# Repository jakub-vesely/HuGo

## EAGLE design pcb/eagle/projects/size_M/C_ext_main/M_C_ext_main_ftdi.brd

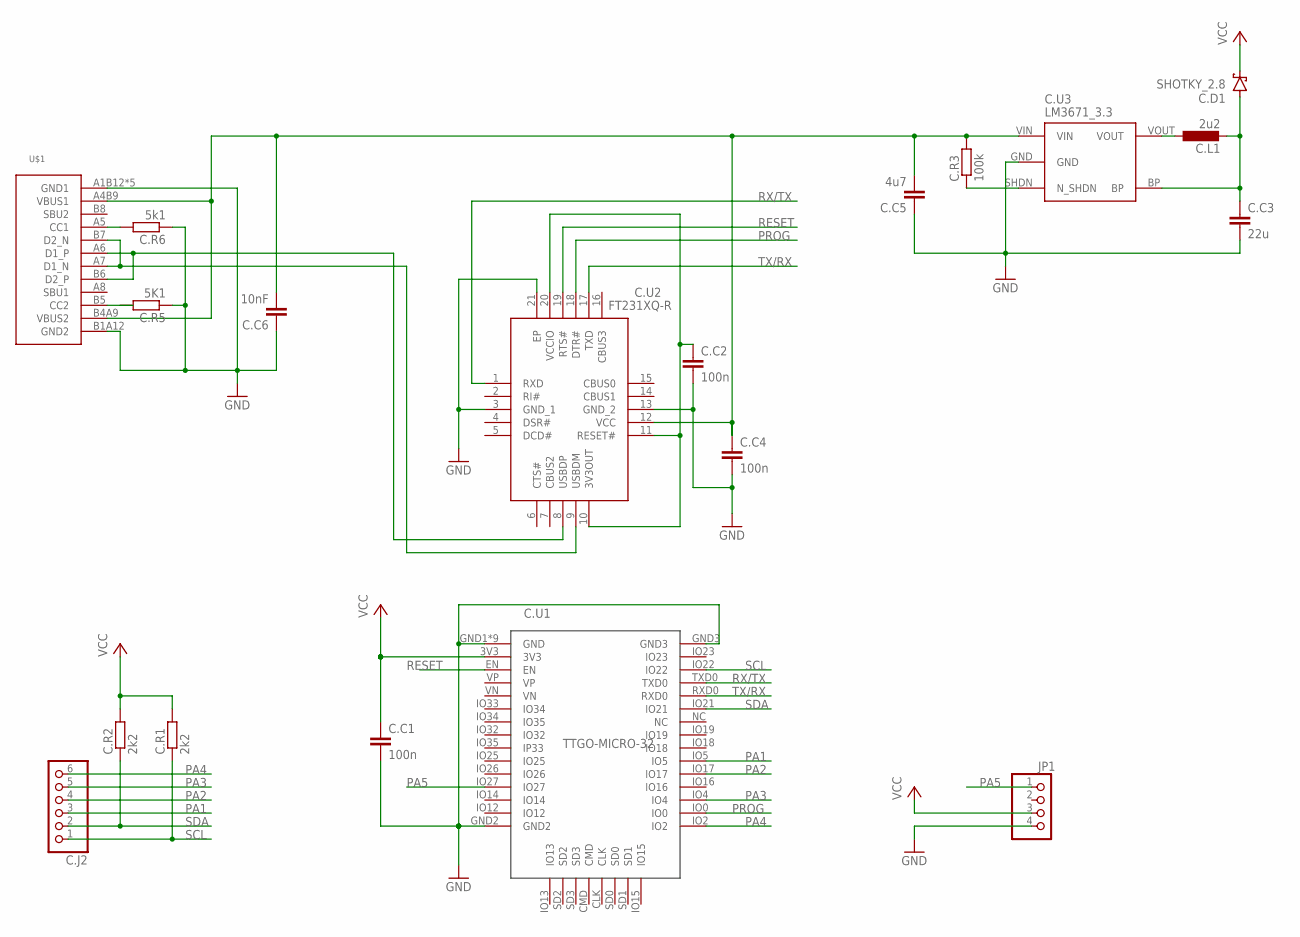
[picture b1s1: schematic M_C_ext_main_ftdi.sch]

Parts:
C.C1, C.C2, C.C4: 100n; C0603
C.C3: 22u; C0805
C.C5: 4u7; C0603
C.C6: 10nF; C0603
C.D1: SHOTKY_2.8
C.J2: PINHD-1X6; 1X06
C.L1: 2u2; L3230M
C.R1, C.R2: 2k2; R0603
C.R3: 100k; R0603
C.R5: 5K1; R0603
C.R6: 5k1; R0603
C.U1: TTGO-MICRO-32
C.U2: FT231XQ-R; QFN50P400X400X80-21N
C.U3: LM3671_3.3; SOT32-5
JP1: PINHD-1X4; 1X04
U$1: USB-C

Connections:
GND: C.C1.2, C.C2.2, C.C3.2, C.C4.2, C.C5.1, C.C6.1, C.R5.1, C.R6.1, C.U1.GND1 (GND), C.U1.GND2, C.U1.GND3, C.U1.GND4 (GND), C.U1.GND5 (GND), C.U1.GND6 (GND), C.U1.GND7 (GND), C.U1.GND8 (GND), C.U1.GND9 (GND), C.U1.GND10 (GND), C.U1.GND11 (GND), C.U2.3 (GND_1), C.U2.13 (GND_2), C.U2.21 (EP), C.U3.GND, JP1.4, U$1.A1B12 (GND1), U$1.B1A12 (GND2), U$1.SH1 (GND1), U$1.SH2 (GND1), U$1.SH3 (GND1), U$1.SH4 (GND1)
unnamed: C.U2.9 (USBDM), U$1.A7 (D1_N), U$1.B7 (D2_N)
unnamed: C.U2.8 (USBDP), U$1.A6 (D1_P), U$1.B6 (D2_P)
unnamed: C.R6.2, U$1.A5 (CC1)
unnamed: C.R5.2, U$1.B5 (CC2)
unnamed: C.C3.1, C.D1.A, C.L1.2, C.U3.BP
unnamed: C.L1.1, C.U3.VOUT
unnamed: C.R3.1, C.U3.SHDN (N_SHDN)
unnamed: C.C2.1, C.U2.10 (3V3OUT), C.U2.11 (RESET#), C.U2.20 (VCCIO)
PA1: C.J2.3, C.U1.IO5
PA2: C.J2.4, C.U1.IO17
PA3: C.J2.5, C.U1.IO4
PA4: C.J2.6, C.U1.IO2
PA5: C.U1.IO27, JP1.1
PROG: C.U1.IO0, C.U2.18 (DTR#)
RESET: C.U1.EN, C.U2.19 (RTS#)
RX/TX: C.U1.TXD0, C.U2.1 (RXD)
SCL: C.J2.1, C.R1.1, C.U1.IO22
SDA: C.J2.2, C.R2.1, C.U1.IO21
TX/RX: C.U1.RXD0, C.U2.17 (TXD)
VCC: C.C1.1, C.D1.K (C), C.R1.2, C.R2.2, C.U1.3V3, JP1.3
VUSB: C.C4.1, C.C5.2, C.C6.2, C.R3.2, C.U2.12 (VCC), C.U3.VIN, U$1.A4B9 (VBUS1), U$1.B4A9 (VBUS2)

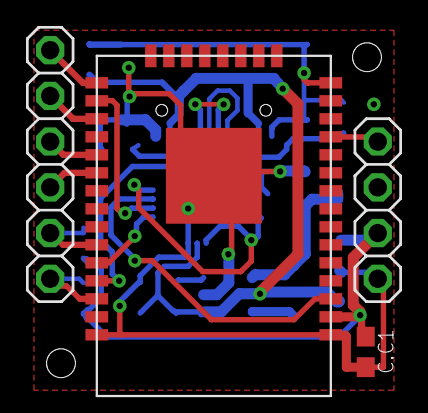
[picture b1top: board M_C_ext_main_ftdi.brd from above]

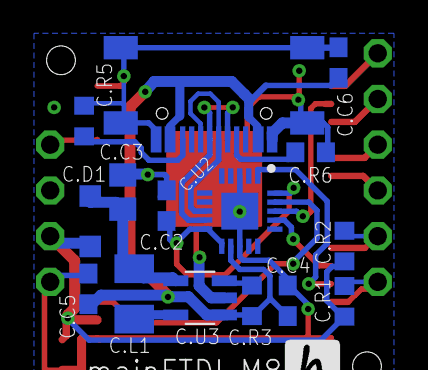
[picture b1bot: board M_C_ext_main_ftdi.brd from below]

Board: 2 copper layers, 19 parts (15 on the bottom side), 22 nets.

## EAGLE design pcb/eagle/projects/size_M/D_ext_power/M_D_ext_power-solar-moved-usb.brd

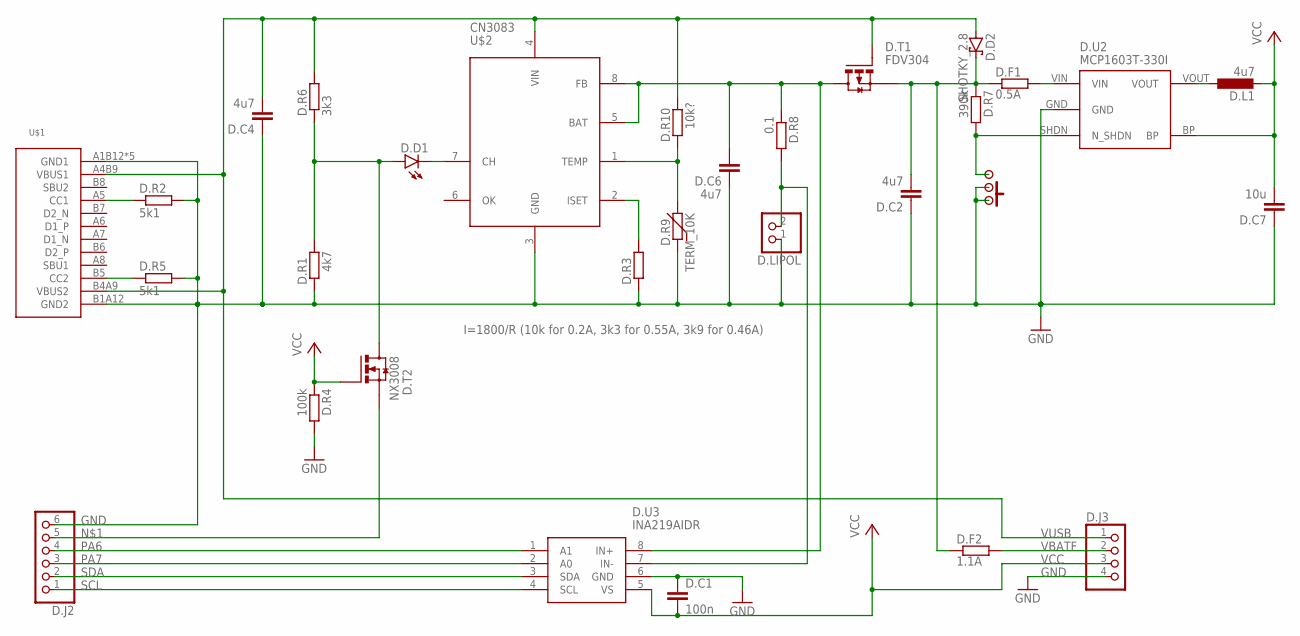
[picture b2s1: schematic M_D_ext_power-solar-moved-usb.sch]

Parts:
D.C1: 100n; C0603
D.C2, D.C4, D.C6: 4u7; C0603
D.C7: 10u; C0805
D.D1: LEDCHIP-LED0603; CHIP-LED0603
D.D2: SHOTKY_2.8
D.F1: 0.5A; R0805
D.F2: 1.1A; R0805
D.J2: PINHD-1X6; 1X06
D.J3: PINHD-1X4; 1X04
D.L1: 4u7; L3230M
D.LIPOL: PINHD-1X2; 1X02
D.ON/OFF/RESET: SWITCH
D.R1: 4k7; R0603
D.R2, D.R5: 5k1; R0603
D.R3: I=1800/R (10k for 0.2A, 3k3 for 0.55A, 3k9 for 0.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; R0603
D.R4: 100k; R0603
D.R6: 3k3; R0603
D.R7: 390k; R0603
D.R8: 0.1; R0805
D.R9: TERM_10K; THERM
D.R10: 10k?; R0603
D.T1: FDV304; SO23
D.T2: NX3008; SO23
D.U2: MCP1603T-330I; SOT32-5
D.U3: INA219AIDR; SOIC127P600X175-8N
U$1: USB-C
U$2: CN3083; SOP8

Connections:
GND: D.C1.1, D.C2.1, D.C4.1, D.C6.1, D.C7.1, D.J2.6, D.J3.4, D.LIPOL.1, D.ON/OFF/RESET.P$1, D.ON/OFF/RESET.P$2, D.ON/OFF/RESET.P$4, D.R1.1, D.R2.2, D.R3.1, D.R4.2, D.R5.2, D.R9.1, D.U2.GND, D.U3.6 (GND), U$1.A1B12 (GND1), U$1.B1A12 (GND2), U$1.SH1 (GND1), U$1.SH2 (GND1), U$1.SH3 (GND1), U$1.SH4 (GND1), U$2.3 (GND)
IN+: D.LIPOL.2, D.R8.2, D.U3.7 (IN-)
IN-: D.C6.2, D.R8.1, D.T1.D, D.U3.8 (IN+), U$2.5 (BAT), U$2.8 (FB)
unnamed: D.J2.5, D.T2.S
unnamed: D.L1.1, D.U2.VOUT
unnamed: D.D1.C1 (C), U$2.7 (CH)
unnamed: D.R5.1, U$1.B5 (CC2)
unnamed: D.ON/OFF/RESET.P$3, D.ON/OFF/RESET.P$5, D.R7.2, D.U2.SHDN (N_SHDN)
unnamed: D.R2.1, U$1.A5 (CC1)
unnamed: D.R3.2, U$2.2 (ISET)
unnamed: D.R9.2, D.R10.1, U$2.1 (TEMP)
unnamed: D.F1.2, D.U2.VIN
PA3: D.D1.A1 (A), D.R1.2, D.R6.1, D.T2.D
PA6: D.J2.4, D.U3.1 (A1)
PA7: D.J2.3, D.U3.2 (A0)
SCL: D.J2.1, D.U3.4 (SCL)
SDA: D.J2.2, D.U3.3 (SDA)
VBATF: D.F2.2, D.J3.2
VCC: D.C1.2, D.C7.2, D.J3.3, D.L1.2, D.R4.1, D.T2.G, D.U2.BP, D.U3.5 (VS)
VMOT: D.C2.2, D.D2.K (C), D.F1.1, D.F2.1, D.R7.1, D.T1.S
VUSB: D.C4.2, D.D2.A, D.J3.1, D.R6.2, D.R10.2, D.T1.G, U$1.A4B9 (VBUS1), U$1.B4A9 (VBUS2), U$2.4 (VIN)

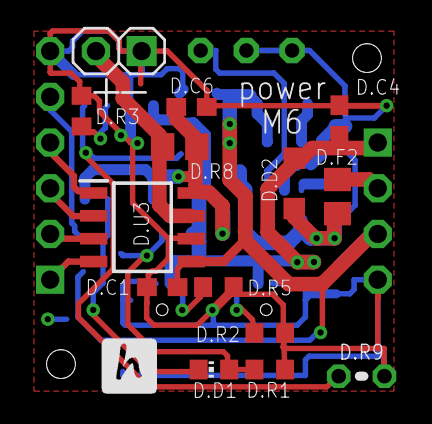
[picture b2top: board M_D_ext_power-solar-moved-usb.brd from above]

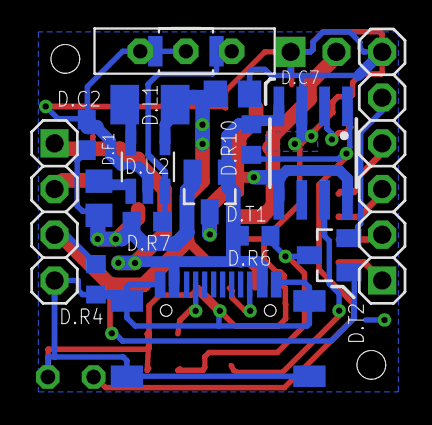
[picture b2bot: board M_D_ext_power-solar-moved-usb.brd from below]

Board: 2 copper layers, 30 parts (16 on the bottom side), 21 nets.

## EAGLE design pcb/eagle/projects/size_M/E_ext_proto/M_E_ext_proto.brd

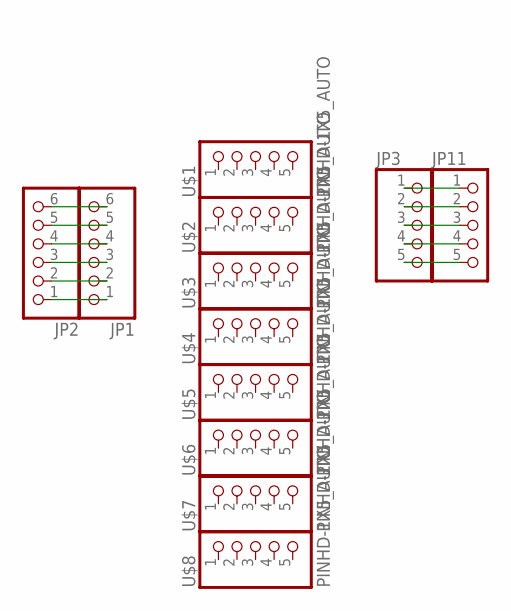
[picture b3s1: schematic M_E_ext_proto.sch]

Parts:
JP1, JP2: PINHD-1X6; 1X06
JP3, JP11: PINHD-1X5; 1X05
U$1, U$2, U$3, U$4, U$5, U$6, U$7, U$8: PINHD-1X5_AUTO; 1X5_AUTO

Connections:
GND: JP3.4, JP11.4
unnamed: JP1.5, JP2.5
unnamed: JP1.4, JP2.4
unnamed: JP1.3, JP2.3
unnamed: JP1.2, JP2.2
unnamed: JP1.1, JP2.1
unnamed: JP3.5, JP11.5
unnamed: JP3.2, JP11.2
unnamed: JP3.1, JP11.1
unnamed: JP1.6, JP2.6
unnamed: JP3.3, JP11.3

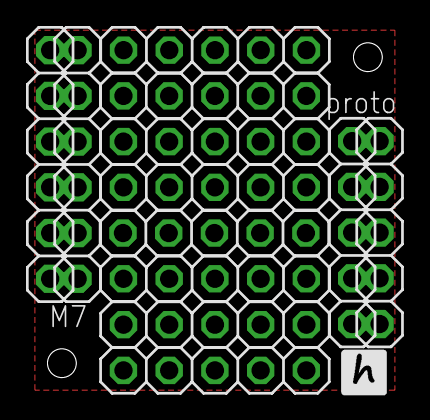
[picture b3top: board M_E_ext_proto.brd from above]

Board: 2 copper layers, 12 parts (0 on the bottom side), 11 nets.

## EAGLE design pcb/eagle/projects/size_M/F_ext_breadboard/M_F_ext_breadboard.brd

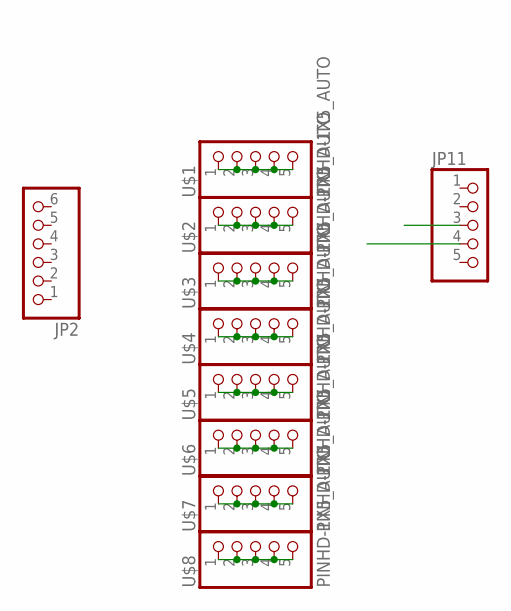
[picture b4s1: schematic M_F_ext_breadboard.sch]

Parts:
JP2: PINHD-1X6; 1X06
JP11: PINHD-1X5; 1X05
U$1, U$2, U$3, U$4, U$5, U$6, U$7, U$8: PINHD-1X5_AUTO; 1X5_AUTO

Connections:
GND: JP11.4
unnamed: U$1.1, U$1.2, U$1.3, U$1.4, U$1.5
unnamed: U$2.1, U$2.2, U$2.3, U$2.4, U$2.5
unnamed: U$3.1, U$3.2, U$3.3, U$3.4, U$3.5
unnamed: U$4.1, U$4.2, U$4.3, U$4.4, U$4.5
unnamed: U$5.1, U$5.2, U$5.3, U$5.4, U$5.5
unnamed: U$6.1, U$6.2, U$6.3, U$6.4, U$6.5
unnamed: U$7.1, U$7.2, U$7.3, U$7.4, U$7.5
unnamed: U$8.1, U$8.2, U$8.3, U$8.4, U$8.5
VDD: JP11.3

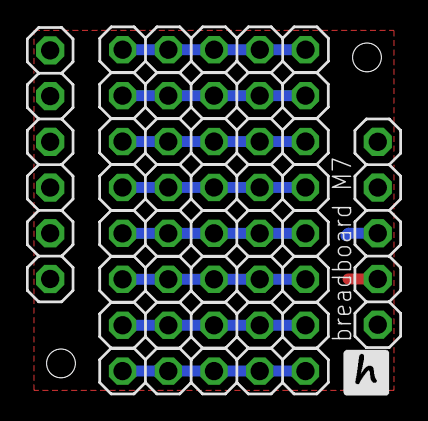
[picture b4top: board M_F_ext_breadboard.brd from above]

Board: 2 copper layers, 10 parts (0 on the bottom side), 8 nets.

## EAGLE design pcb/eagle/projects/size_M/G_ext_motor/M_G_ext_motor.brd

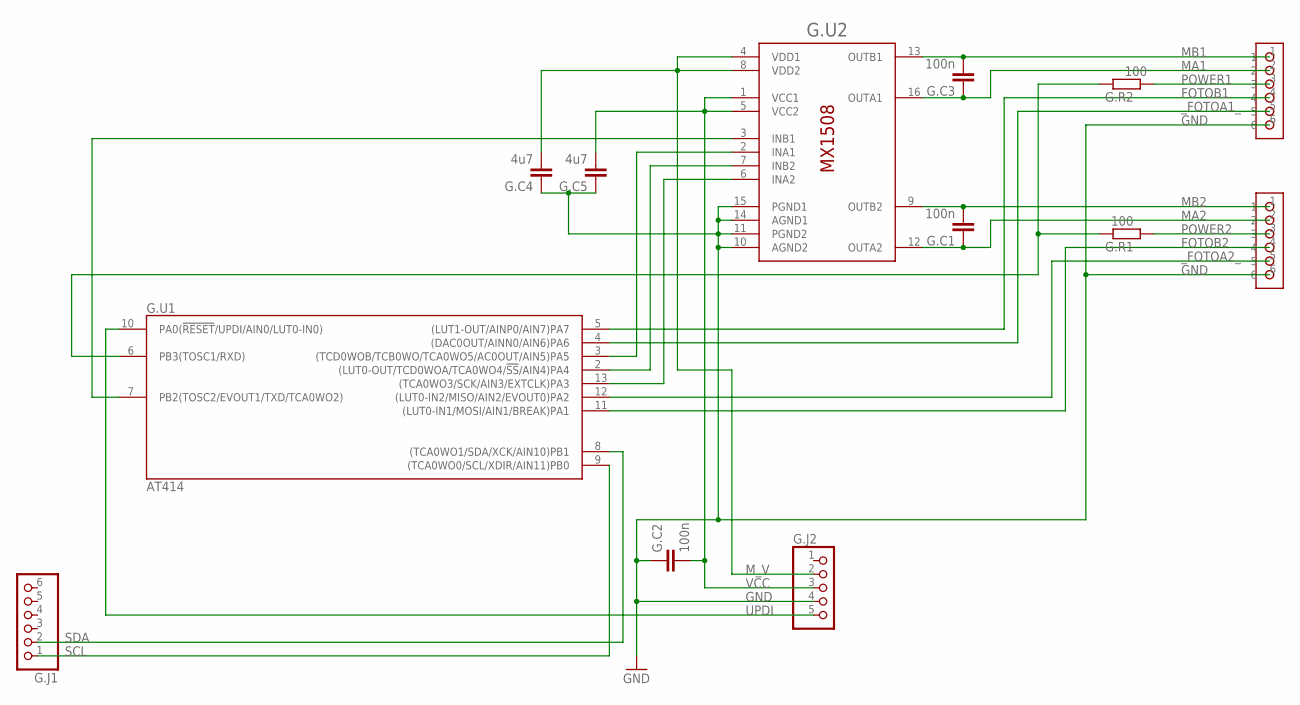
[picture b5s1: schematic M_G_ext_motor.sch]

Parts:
G.C1, G.C2, G.C3: 100n; C0603
G.C4, G.C5: 4u7; C0603
G.J1: PINHD-1X6; 1X06
G.J2: PINHD-1X5; 1X05
G.J3, G.MOTO1: A1250WR-6
G.R1, G.R2: 100; R0603
G.U1: AT414; SO14
G.U2: MX1508; SOP16

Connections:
FOTOB1: G.MOTO1.4, G.U1.5 ((LUT1-OUT/AINP0/AIN7)PA7)
FOTOB2: G.J3.4, G.U1.11 ((LUT0-IN1/MOSI/AIN1/BREAK)PA1)
GND: G.C2.1, G.C4.1, G.C5.1, G.J2.4, G.J3.6, G.J3.$1 (GND), G.J3.$2 (GND), G.MOTO1.6, G.MOTO1.$1 (GND), G.MOTO1.$2 (GND), G.U1.14 (GND), G.U2.10 (AGND2), G.U2.11 (PGND2), G.U2.14 (AGND1), G.U2.15 (PGND1)
INA1: G.U1.3 ((TCD0WOB/TCB0WO/TCA0WO5/AC0OUT/AIN5)PA5), G.U2.2 (INA1)
INA2: G.U1.13 ((TCA0WO3/SCK/AIN3/EXTCLK)PA3), G.U2.6 (INA2)
INB1: G.U1.7 (PB2(TOSC2/EVOUT1/TXD/TCA0WO2)), G.U2.3 (INB1)
INB2: G.U1.2 ((LUT0-OUT/TCD0WOA/TCA0WO4/!SS!/AIN4)PA4), G.U2.7 (INB2)
MA1: G.C3.1, G.MOTO1.2, G.U2.16 (OUTA1)
MA2: G.C1.1, G.J3.2, G.U2.12 (OUTA2)
MB1: G.C3.2, G.MOTO1.1, G.U2.13 (OUTB1)
MB2: G.C1.2, G.J3.1, G.U2.9 (OUTB2)
M_V: G.C4.2, G.J2.2, G.U2.4 (VDD1), G.U2.8 (VDD2)
POWER1: G.MOTO1.3, G.R2.1
POWER2: G.J3.3, G.R1.1
POWER_LED: G.R1.2, G.R2.2, G.U1.6 (PB3(TOSC1/RXD))
SCL: G.J1.1, G.U1.9 ((TCA0WO0/SCL/XDIR/AIN11)PB0)
SDA: G.J1.2, G.U1.8 ((TCA0WO1/SDA/XCK/AIN10)PB1)
UPDI: G.J2.5, G.U1.10 (PA0(!RESET!/UPDI/AIN0/LUT0-IN0))
VCC: G.C2.2, G.C5.2, G.J2.3, G.U1.1 (VCC), G.U2.1 (VCC1), G.U2.5 (VCC2)
_FOTOA1_: G.MOTO1.5, G.U1.4 ((DAC0OUT/AINN0/AIN6)PA6)
_FOTOA2_: G.J3.5, G.U1.12 ((LUT0-IN2/MISO/AIN2/EVOUT0)PA2)

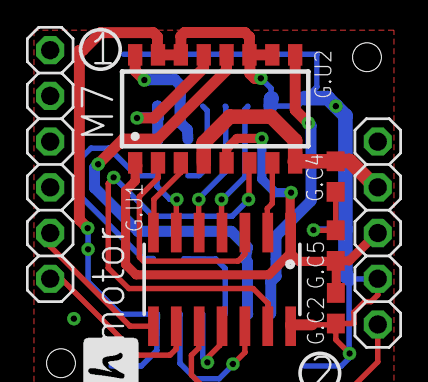
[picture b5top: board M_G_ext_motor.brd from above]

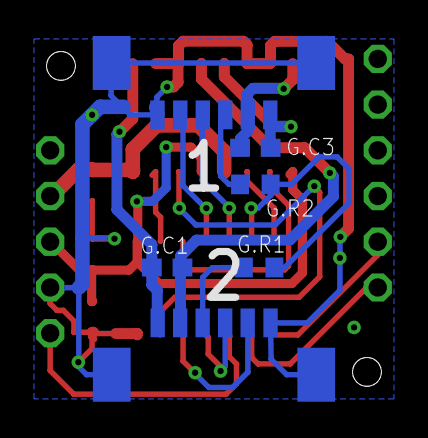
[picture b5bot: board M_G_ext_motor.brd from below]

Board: 2 copper layers, 13 parts (6 on the bottom side), 21 nets.
